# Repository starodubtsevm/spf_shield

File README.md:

# spf_shield
Hardware. SPF Arduino Uno Shield

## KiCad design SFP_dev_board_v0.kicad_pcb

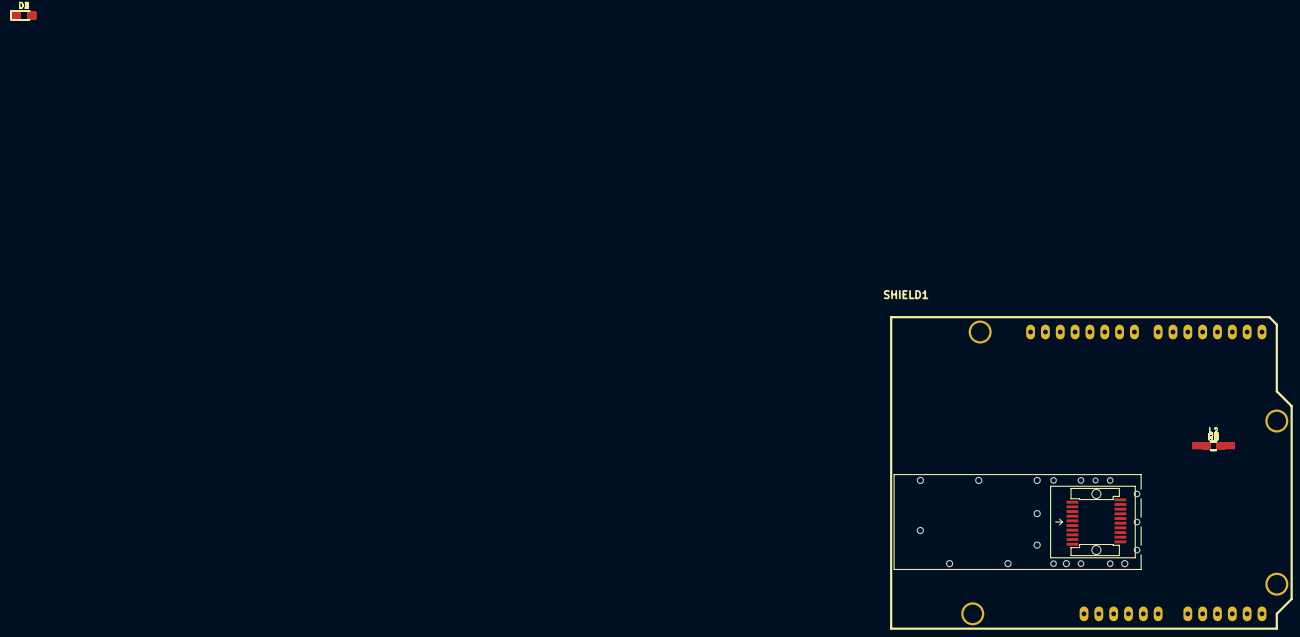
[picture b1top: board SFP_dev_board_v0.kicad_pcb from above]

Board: 2 copper layers, 20 parts (0 on the bottom side), 17 nets, no tracks yet.

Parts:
C1, C3, C5: 0.1u 16V; C_0805_HandSoldering
D1, D2, D3, D4: LED; LED_0805_HandSoldering
L1, L2: 4.7u; Choke_SMD_1206_Handsoldering
P1: CONN_02X10; TE_1367073-1
P2: SFP CAGE; sfp-cage-msa
R1, R2, R3, R4: 4,7k; R_0603_HandSoldering
R5, R6, R7, R8: 1,0k; R_0603_HandSoldering
SHIELD1: ARDUINO_SHIELD; ARDUINO SHIELD

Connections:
3.3V: R1.1, R2.1, R3.1, R4.1, R5.1, R6.1, R7.1, R8.1
+3.3V: C5.1, L1.1, L2.1
GND: C1.2, C3.2, C5.2, P1.1, P1.10, P1.11, P1.14, P1.17, P1.20, SHIELD1.GND1, SHIELD1.GND2, SHIELD1.GND3
unnamed: D1.1, SHIELD1.13
unnamed: D1.2, R5.2
unnamed: D2.1, SHIELD1.12
unnamed: D2.2, R6.2
unnamed: D3.1, SHIELD1.11
unnamed: D3.2, R7.2
unnamed: D4.1, SHIELD1.6
unnamed: D4.2, R8.2
RLOS: P1.8, R4.2
SCL: P1.5, R1.2, SHIELD1.AD5
SDA: P1.4, R2.2, SHIELD1.AD4
TX_Fault: P1.2, R3.2
VccRx: C1.1, L1.2, P1.15
VccTx: C3.1, L2.2, P1.16

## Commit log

2017-11-18 power Ic added
2017-11-18 test3
2017-11-18 SN65EPT22 added
2017-11-18 some docs added
2017-11-18 buffers added
2017-11-19 schematic complete
2017-11-20 небольшие изменения
2017-11-20 test
2017-11-20 buffers
